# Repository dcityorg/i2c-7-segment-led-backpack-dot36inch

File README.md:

#### I²C 7 Segment LED Backpack Board (.36 inch LEDs)

<div style="text-align: center;">
<div style="display: inline-block; margin-right: 5px;">

</div>
<div style="display: inline-block; margin-right: 5px;">

</div>
<div style="display: inline-block; margin-right: 5px;">

</div>
</div>

**[This link has details](https://www.dcity.org/portfolio/i2c-7-segment-led-backpack-dot36inch/) including**
* parts lists
* assembly instructions
* jumper configuration
* Arduino, Particle and Raspberry Pi software library usage
* Bare PC boards are available from OSHPark.

**Note: The pictures show the backpack board with Grove type connectors, but they have been changed to [Qwiic](https://www.sparkfun.com/qwiic) connectors.**

**License Information**
Open Source Hardware Design. Our License Information is [here](https://www.dcity.org/license-information/).

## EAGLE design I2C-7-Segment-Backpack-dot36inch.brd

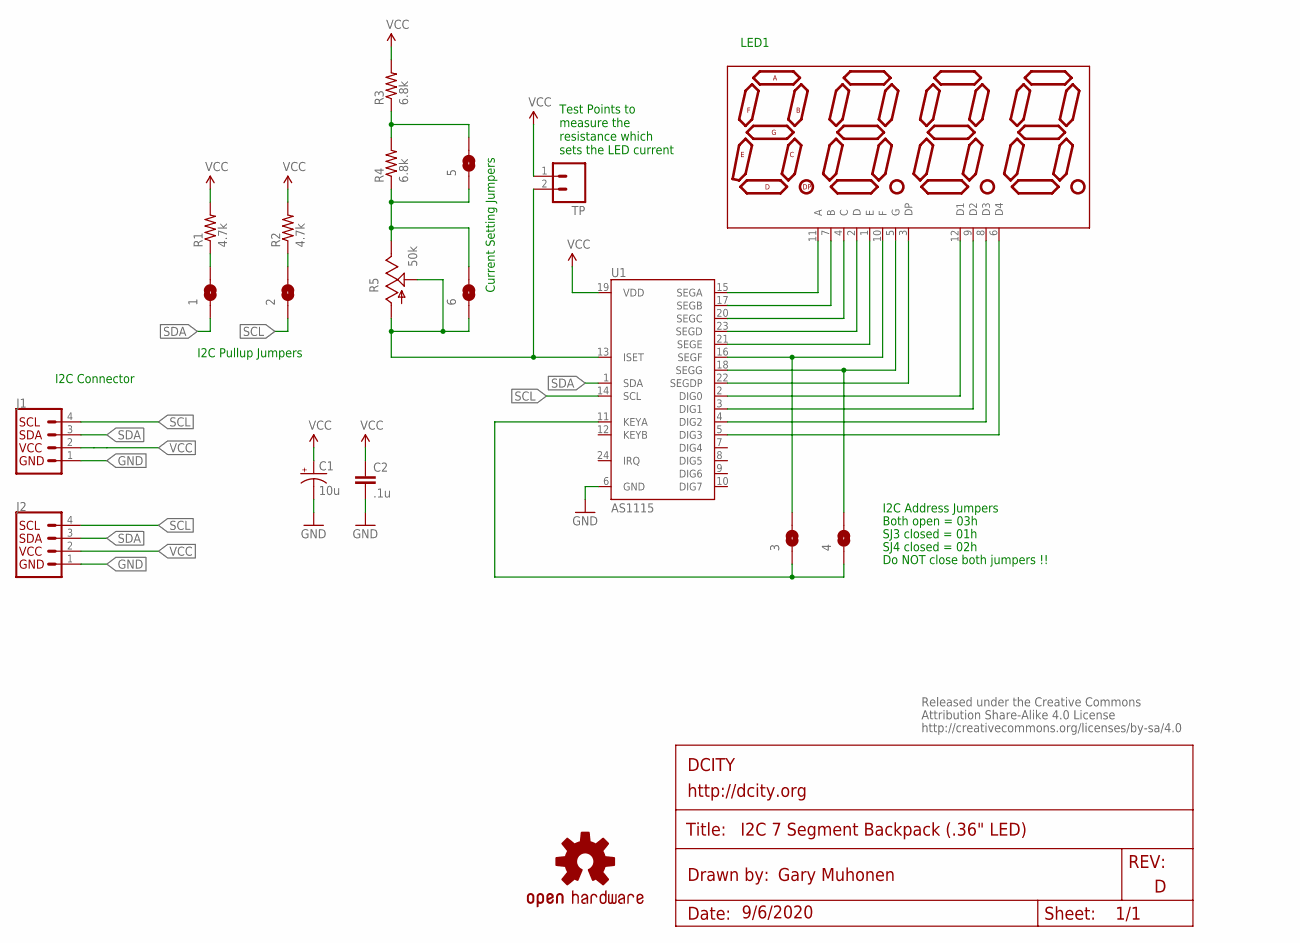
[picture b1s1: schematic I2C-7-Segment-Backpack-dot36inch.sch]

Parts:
1, 2, 3, 4, 5, 6: SOLDERJUMPERNO; SJ_2S-NO
C1: 10u; 0805-POL
C2: .1u; 0805-CAP
DISP1: LED1; 7-SEGMENT-4DIGIT-PT4
J1, J2: QWIIC_RIGHT_ANGLE; JST04_1MM_RA
LOGO1: OSHW-LOGOS; OSHW-LOGO-S
R1, R2: 4.7k; 0805-RES
R3, R4: 6.8k; 0805-RES
R5: 50k; POT-TC33X
TP: M02PTH; 1X02
U1: AS1115; TSSOP24-NO-HS
U$4: CREATIVE_COMMONS

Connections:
GND: C1.-, C2.2, J1.1, J2.1, U1.6 (GND)
unnamed: DISP1.11 (A), U1.15 (SEGA)
unnamed: DISP1.7 (B), U1.17 (SEGB)
unnamed: DISP1.4 (C), U1.20 (SEGC)
unnamed: DISP1.2 (D), U1.23 (SEGD)
unnamed: DISP1.1 (E), U1.21 (SEGE)
unnamed: 3.2, DISP1.10 (F), U1.16 (SEGF)
unnamed: 4.2, DISP1.5 (G), U1.18 (SEGG)
unnamed: DISP1.3 (DP), U1.22 (SEGDP)
unnamed: DISP1.12 (D1), U1.2 (DIG0)
unnamed: DISP1.9 (D2), U1.3 (DIG1)
unnamed: DISP1.8 (D3), U1.4 (DIG2)
unnamed: DISP1.6 (D4), U1.5 (DIG3)
unnamed: 3.1, 4.1, U1.11 (KEYA)
unnamed: 6.1, R5.1 (A), R5.2 (S), TP.2, U1.13 (ISET)
unnamed: 5.1, 6.2, R4.1, R5.3 (E)
unnamed: 5.2, R3.1, R4.2
unnamed: 1.2, R1.1
unnamed: 2.2, R2.1
SCL: 2.1, J1.4, J2.4, U1.14 (SCL)
SDA: 1.1, J1.3, J2.3, U1.1 (SDA)
VCC: C1.+, C2.1, J1.2, J2.2, R1.2, R2.2, R3.2, TP.1, U1.19 (VDD)

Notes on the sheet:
I2C Connector
I2C Pullup Jumpers
Current Setting Jumpers
I2C Address Jumpers
Both open = 03h
SJ3 closed = 01h
SJ4 closed = 02h
Do NOT close both jumpers !!
LED1
Test Points to measure the resistance which sets the LED current

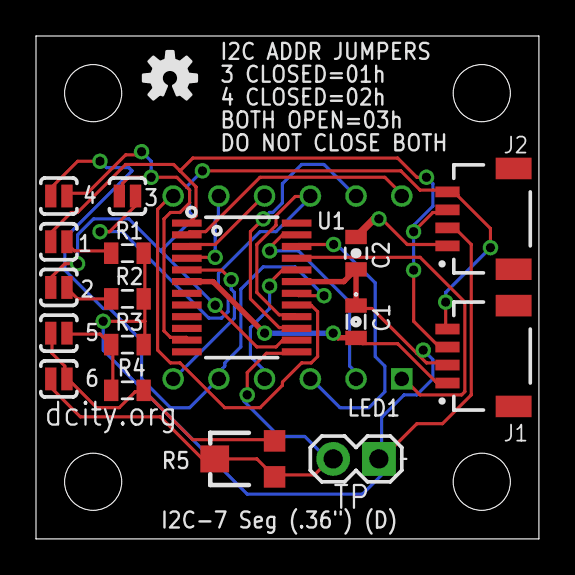
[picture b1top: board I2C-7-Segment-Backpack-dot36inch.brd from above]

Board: 2 copper layers, 27.9 x 27.9 mm, 20 parts (1 on the bottom side), 22 nets.

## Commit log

2016-07-30 First commit - Rev B
2016-07-30 modified .gitignore
2016-07-30 removed .gitignore
2018-09-14 Rev C
2020-10-11 Rev D

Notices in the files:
parts and their libraries:
0: Released under the Creative Commons
0: http://creativecommons.org/licenses/by-sa/4.0
